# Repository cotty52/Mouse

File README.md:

# Custom Wireless Mouse

This project contains software and hardware designs for a custom wireless mouse. This is an initial prototype intended for me to learn about hardware design and embedded software development. I combined hardware and software files into one repository for easier management. As of 2026-04-21, the design supports basic mouse functionality, including movement, button presses, and scrolling, and is powered by a 3.7V Li-ion battery, rechargeable via USB-C.

## File Structure

```
Mouse/
├── Documents/        # Datasheets, bootloader UF2, 3D models
├── Guide/
│   └── README.md     # New machine setup guide
├── KiCad/            # PCB schematics and layout
└── Software/
    ├── PROJECT_GUIDE.md  # Architecture, task tracking, module reference
    └── ...
```

- `Documents` contains datasheets, reference layouts, and documentation for the nRF Connect SDK and Zephyr project.
- `Guide` contains the new machine setup guide (`Guide/README.md`) and dated snapshots of known-good board/config files.
- `KiCad` contains the KiCad project files for the PCB design (schematics, PCB layout, Gerber files).
- `Software` contains firmware source, board definitions, and configuration files. See `Software/PROJECT_GUIDE.md` for details.

## Hardware Design

The hardware design is based on the nRF52840 because of its popularity/availability, built in Bluetooth, low power consumption, and integration with the nRF SDK for software development. The PCB was designed using KiCad and currently relies on a nRF52840 nice!nano microcontroller for higher level development in the early stages. The microcontroller includes a USB-C port for charging and firmware flashing, a charging protection circuit, and enough GPIO for this project. The design also includes a PMW3389 optical sensor for mouse movement, which is supported by the nRF SDK and Zephyr.

### PCB Images

| Full | Front | Back |
|:---:|:---:|:---:|
|  |  |  |

## Software Design

The software is developed using the nRF Connect SDK, which is based on the Zephyr RTOS. The nRF Connect VS Code extension is used for development, which provides a convenient interface for firmware development. The base structure is copied directly from the nRF Desktop sample project, which provides a good starting point for developing a Bluetooth mouse. The sample provides support for Bluetooth connectivity, mouse movement, button presses, and scrolling out of the box, with additional features available to be toggled on/off using the Kconfig GUI. The sample also provides sample mouse configurations as well as a PMW3360 driver, which is similar to the PMW3389. These files serve as a reference for the development of custom hardware and application files for the custom mouse.

## Current Problems

As of 2026-04-27 there are a couple major issues. The primary issue is the nice!nano board itself. While it was a good microcontroller to get started with this project and to learn about the basics, it was sometimes difficult to work with. Even though there are SWD pads on the back of the board, I could not get it to work with my nRF52840-DK. I also could not get bluetooth to work on the nice!nano, which is why I switched to the nRF52840-dongle for the most recent development. The dongle is meant to be a receiver, but it has enough gpio to connect everything; and since it is a nordic product, development was much easier.

The second problem was with the pmw3389 sensor. I have not figured out why it was not working with my PCB, but I was able to get it working with a breakout board. A multimeter showed that the voltage at the VDD pin was not stable and would start below 1.9V, then rise to above 1.9V. This leads me to believe my step-down circuit is wrong; either I got the calculations for the resistors and capacitors wrong, or the buck converter was not soldered properly. I used a microscope and the connections looked good, but it is very small so it's possible there is a cold solder joint or something else I missed.

## Future Improvements

The next step is to design the PCB without the nice!nano which will require using the nRF52840 SoC directly. This will involve further researching the nRF52840 for proper implementation as well as designing power management and charging circuits. I will also need to decide on whether to use an SoC with an included antenna or design one myself.

Becasue of the problems with the pmw3389, I will not use the TPS62821DLCR buck converter. I will probably use a linear step-down regulator instead, which will be less efficient but much simpler to implement.

On the software side, the next step is to develop custom application code for the mouse which will allow users to customize the behavior of the mouse, such as button mapping and sensitivity settings.

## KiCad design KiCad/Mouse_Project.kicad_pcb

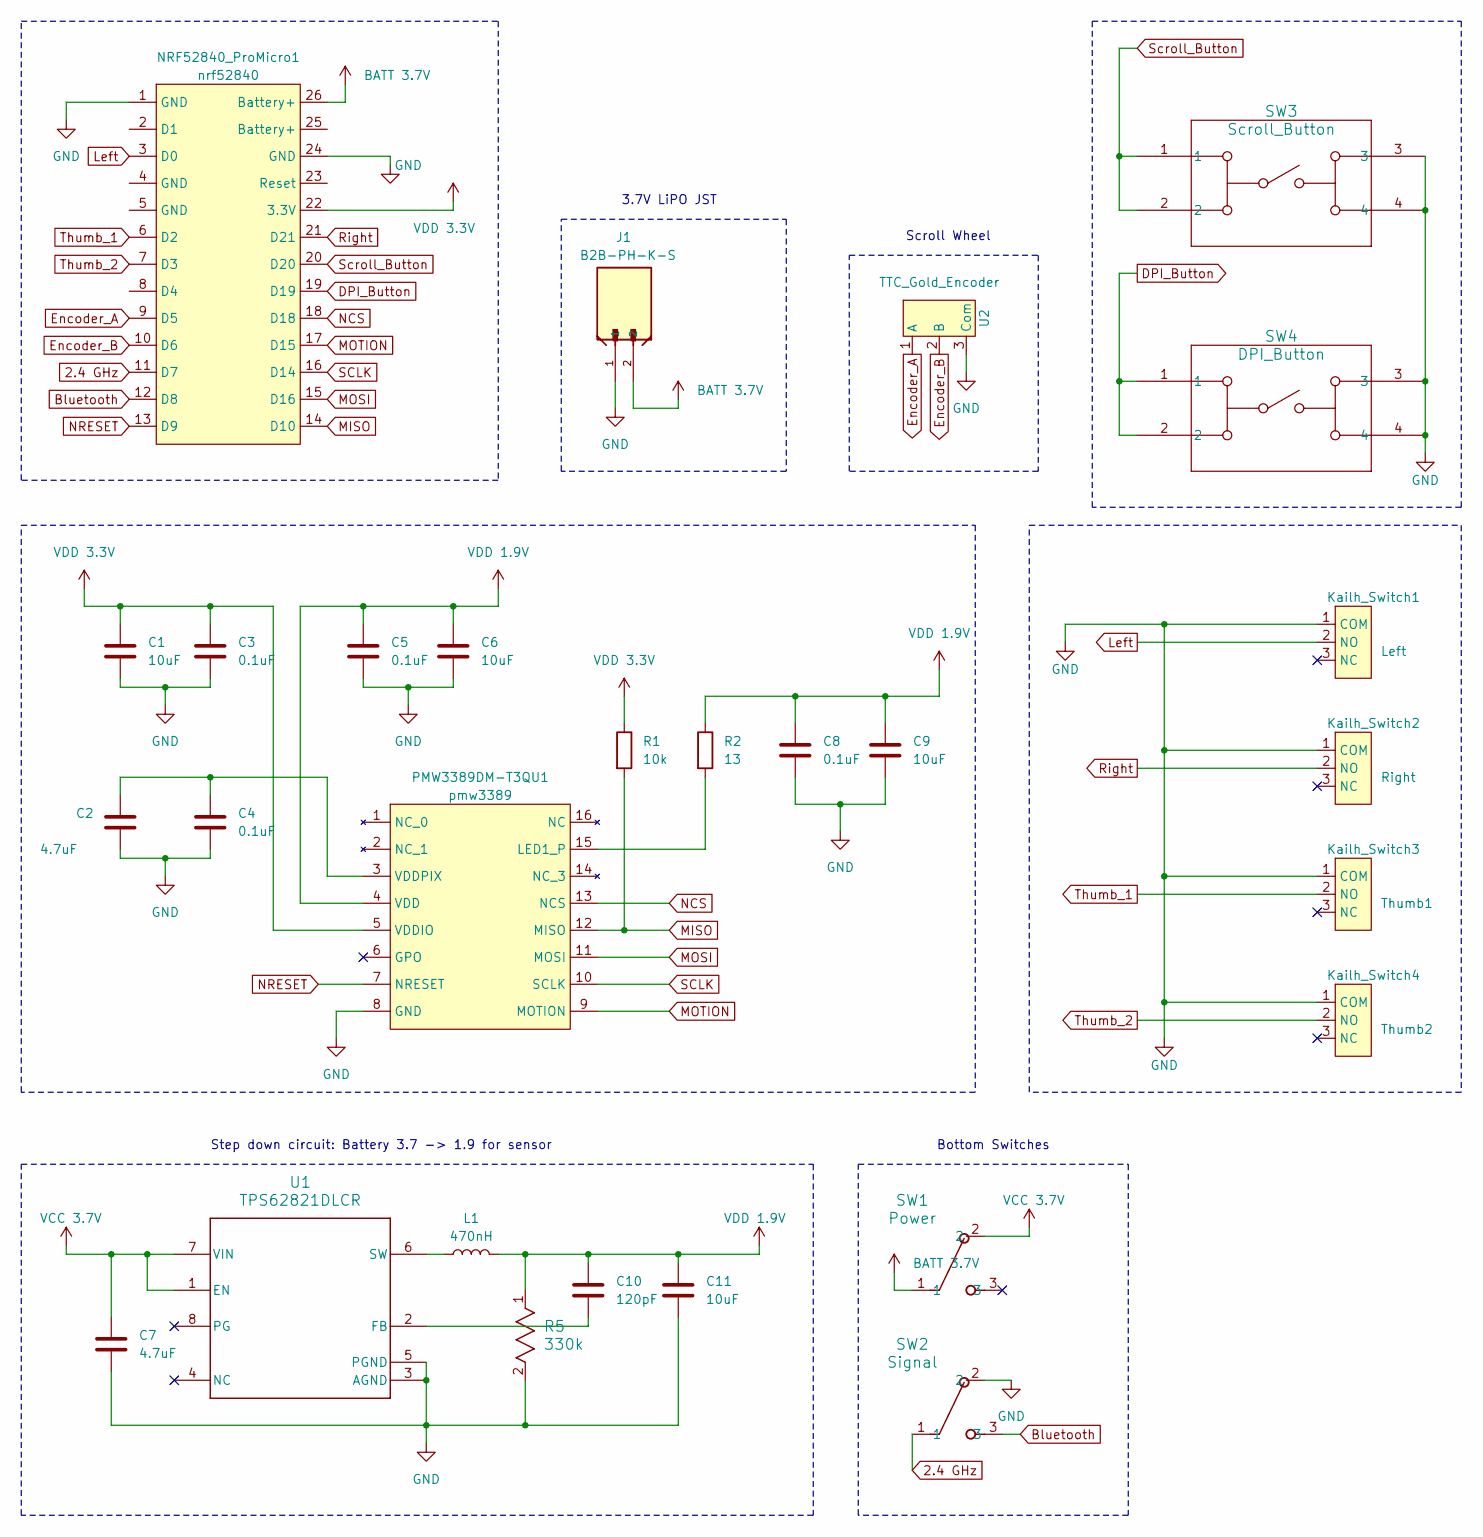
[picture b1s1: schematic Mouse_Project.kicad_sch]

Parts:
C1, C6, C9, C11: 10uF; CL31A106KBHNNNE
C2, C7: 4.7uF; CL31B475KBHNNNE
C3, C4, C5, C8: 0.1uF; C1206C104K5RACTU
C10: 120pF; C0805C121J5GACTU
J1: B2B-PH-K-S; CONN2_B2B-PH-K-S_JST
Kailh_Switch1: Left; Kailh_Switch
Kailh_Switch2: Right; Kailh_Switch
Kailh_Switch3: Thumb1; Kailh_Switch
Kailh_Switch4: Thumb2; Kailh_Switch
L1: 470nH; DFE252012P-1R0M=P2
NRF52840_ProMicro1: nrf52840; nrf52840_promicro
PMW3389DM-T3QU1: pmw3389; pmw3389dm-t3qu
R1: 10k; RC1206FR-0710KL
R2: 13; RC0805N_YAG
R5: 330k; RES_CRGCQ1206F330K_TEC
SW1: Power; SW_1218_EWI
SW2: Signal; SW_1218_EWI
SW3: Scroll_Button; SW4_1825910-B_TEC
SW4: DPI_Button; SW4_1825910-B_TEC
U1: TPS62821DLCR
U2: TTC_Gold_Encoder

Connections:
2.4 GHz: NRF52840_ProMicro1.11 (D7), SW2.1
BATT 3.7V: J1.2, NRF52840_ProMicro1.26 (Battery+), SW1.1
Bluetooth: NRF52840_ProMicro1.12 (D8), SW2.3
DPI_Button: NRF52840_ProMicro1.19 (D19), SW4.1, SW4.2
Encoder_A: NRF52840_ProMicro1.9 (D5), U2.1 (A)
Encoder_B: NRF52840_ProMicro1.10 (D6), U2.2 (B)
GND: C1.2, C2.2, C3.2, C4.2, C5.2, C6.2, C7.2, C8.2, C9.2, C11.2, J1.1, Kailh_Switch1.1 (COM), Kailh_Switch2.1 (COM), Kailh_Switch3.1 (COM), Kailh_Switch4.1 (COM), NRF52840_ProMicro1.1 (GND), NRF52840_ProMicro1.24 (GND), PMW3389DM-T3QU1.8 (GND), R5.2, SW2.2, SW3.3, SW3.4, SW4.3, SW4.4, U1.3 (AGND), U1.5 (PGND), U2.3 (Com)
Left: Kailh_Switch1.2 (NO), NRF52840_ProMicro1.3 (D0)
MISO: NRF52840_ProMicro1.14 (D10), PMW3389DM-T3QU1.12 (MISO), R1.2
MOSI: NRF52840_ProMicro1.15 (D16), PMW3389DM-T3QU1.11 (MOSI)
MOTION: NRF52840_ProMicro1.17 (D15), PMW3389DM-T3QU1.9 (MOTION)
NCS: NRF52840_ProMicro1.18 (D18), PMW3389DM-T3QU1.13 (NCS)
NRESET: NRF52840_ProMicro1.13 (D9), PMW3389DM-T3QU1.7 (NRESET)
unnamed: PMW3389DM-T3QU1.15 (LED1_P), R2.2
unnamed: C2.1, C4.1, PMW3389DM-T3QU1.3 (VDDPIX)
unnamed: C10.2, U1.2 (FB)
unnamed: L1.1, U1.6 (SW)
Right: Kailh_Switch2.2 (NO), NRF52840_ProMicro1.21 (D21)
SCLK: NRF52840_ProMicro1.16 (D14), PMW3389DM-T3QU1.10 (SCLK)
Scroll_Button: NRF52840_ProMicro1.20 (D20), SW3.1, SW3.2
Thumb_1: Kailh_Switch3.2 (NO), NRF52840_ProMicro1.6 (D2)
Thumb_2: Kailh_Switch4.2 (NO), NRF52840_ProMicro1.7 (D3)
VCC 3.7V: C7.1, SW1.2, U1.1 (EN), U1.7 (VIN)
VDD 1.9V: C5.1, C6.1, C8.1, C9.1, C10.1, C11.1, L1.2, PMW3389DM-T3QU1.4 (VDD), R2.1, R5.1
VDD 3.3V: C1.1, C3.1, NRF52840_ProMicro1.22 (3.3V), PMW3389DM-T3QU1.5 (VDDIO), R1.1

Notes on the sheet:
Step down circuit: Battery 3.7 -> 1.9 for sensor
Scroll Wheel
Bottom Switches
3.7V LiPO JST

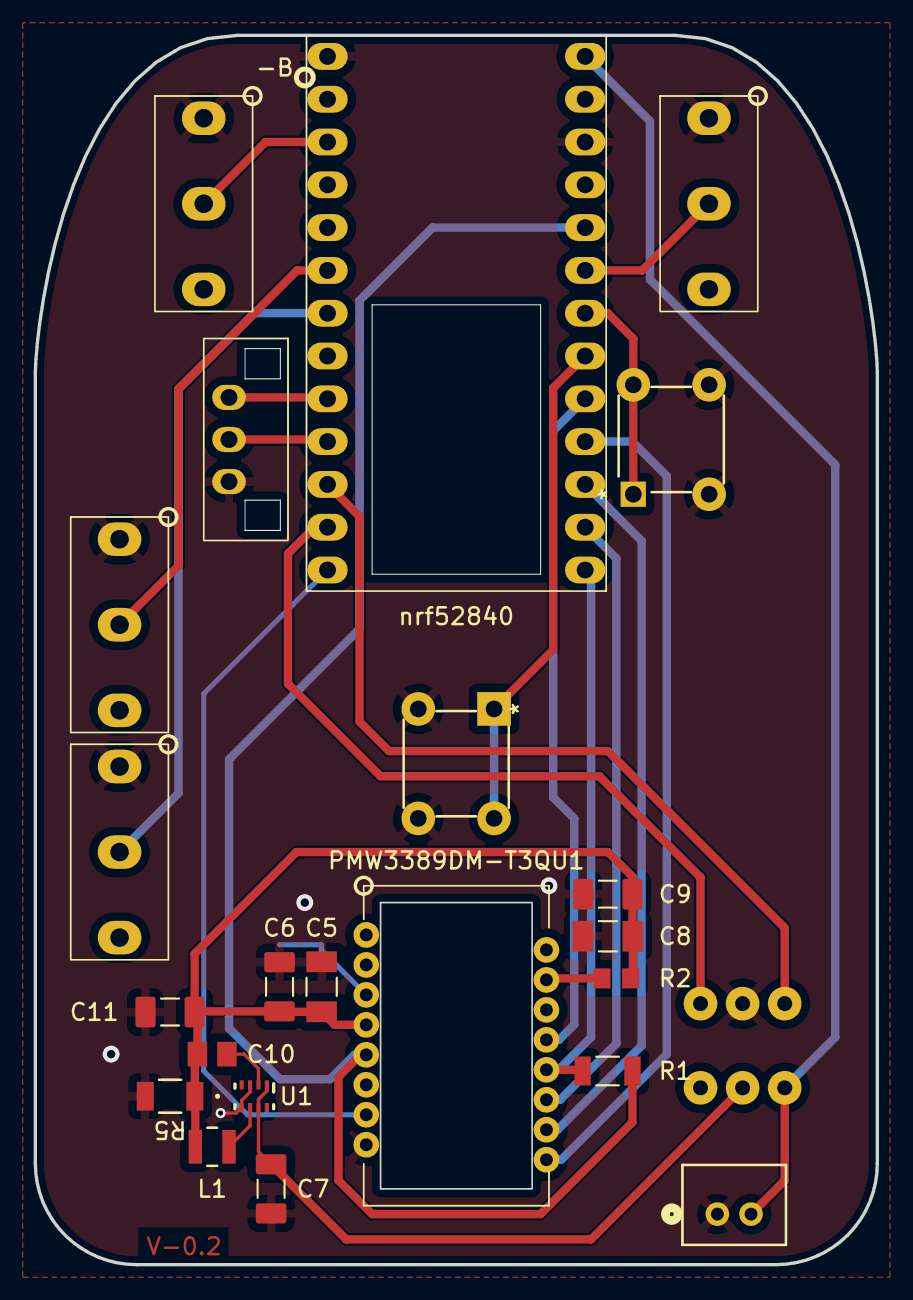
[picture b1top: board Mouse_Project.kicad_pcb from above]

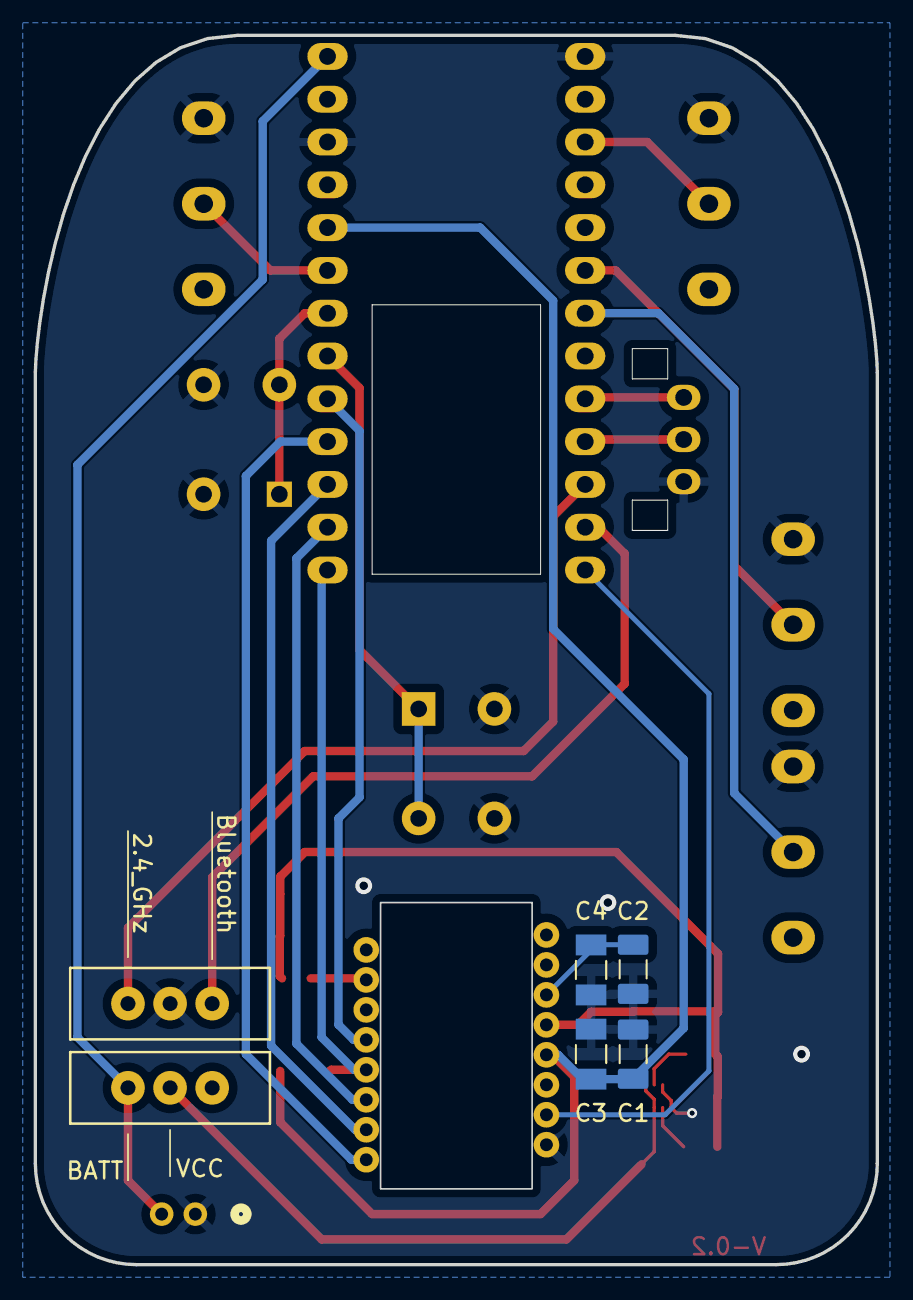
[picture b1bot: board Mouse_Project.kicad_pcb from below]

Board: 2 copper layers, 50.0 x 73.0 mm, 28 parts (6 on the bottom side), 25 nets.

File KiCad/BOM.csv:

"Reference","Value","Qty","Datasheet","Footprint","DNP"
"C1,C6,C9,C11","10uF","4","~","CL21A106KOQNNNE:CAP_CL21_SAM",""
"C2","4.7uF/10V","1","~","CL10A475KP8NNNC:CAP_0603_CL10A_1P6XP8_SAM",""
"C3,C4,C5,C8","0.1uF","4","~","CL10B104KB8NNNC:CAP_CL10_SAM",""
"C7","4.7uF","1","~","CL10A475KP8NNNC:CAP_0603_CL10A_1P6XP8_SAM",""
"C10","120pF","1","~","GRM0335C1H121JA01D:G-033_MUR",""
"J1","B2B-PH-K-S","1","","B2B-PH-K-S:CONN2_B2B-PH-K-S_JST",""
"Kailh_Switch1","Left","1","","Kailh_Switch:Kailh_Switch",""
"Kailh_Switch2","Right","1","","Kailh_Switch:Kailh_Switch",""
"Kailh_Switch3","Thumb1","1","","Kailh_Switch:Kailh_Switch",""
"Kailh_Switch4","Thumb2","1","","Kailh_Switch:Kailh_Switch",""
"L1","470nH","1","~","CIGT201610EHR47MNE:RES_CIGT201610",""
"NRF52840_ProMicro1","nrf52840","1","","nrf52840_promicro:nrf52840_promicro",""
"PMW3389DM-T3QU1","pmw3389","1","","pmw3389dm-t3qu:pmw3389dm-t3qu",""
"R1","10k","1","~","RC1005F103CS:RES_1005_SAM",""
"R2","13","1","~","RC0805FR_0713RL:RC0805N_YAG",""
"R5","CRGCQ1206F330K","1","CRGCQ1206F330K","RES_CRGCQ1206F330K_TEC",""
"SW1","Power","1","EG1218","SW_1218_EWI",""
"SW2","Signal","1","EG1218","SW_1218_EWI",""
"SW3","Scroll_Button","1","1825910-6","1825910-6:SW4_1825910-B_TEC",""
"SW4","DPI_Button","1","1825910-6","1825910-6:SW4_1825910-B_TEC",""
"U1","TPS62821DLCR","1","TPS62821DLCR","TPS62821DLCR:TPS62821DLCR",""
"U2","TTC_Gold_Encoder","1","","TTC_Gold_Encoder:TTC_Gold_Encoder",""

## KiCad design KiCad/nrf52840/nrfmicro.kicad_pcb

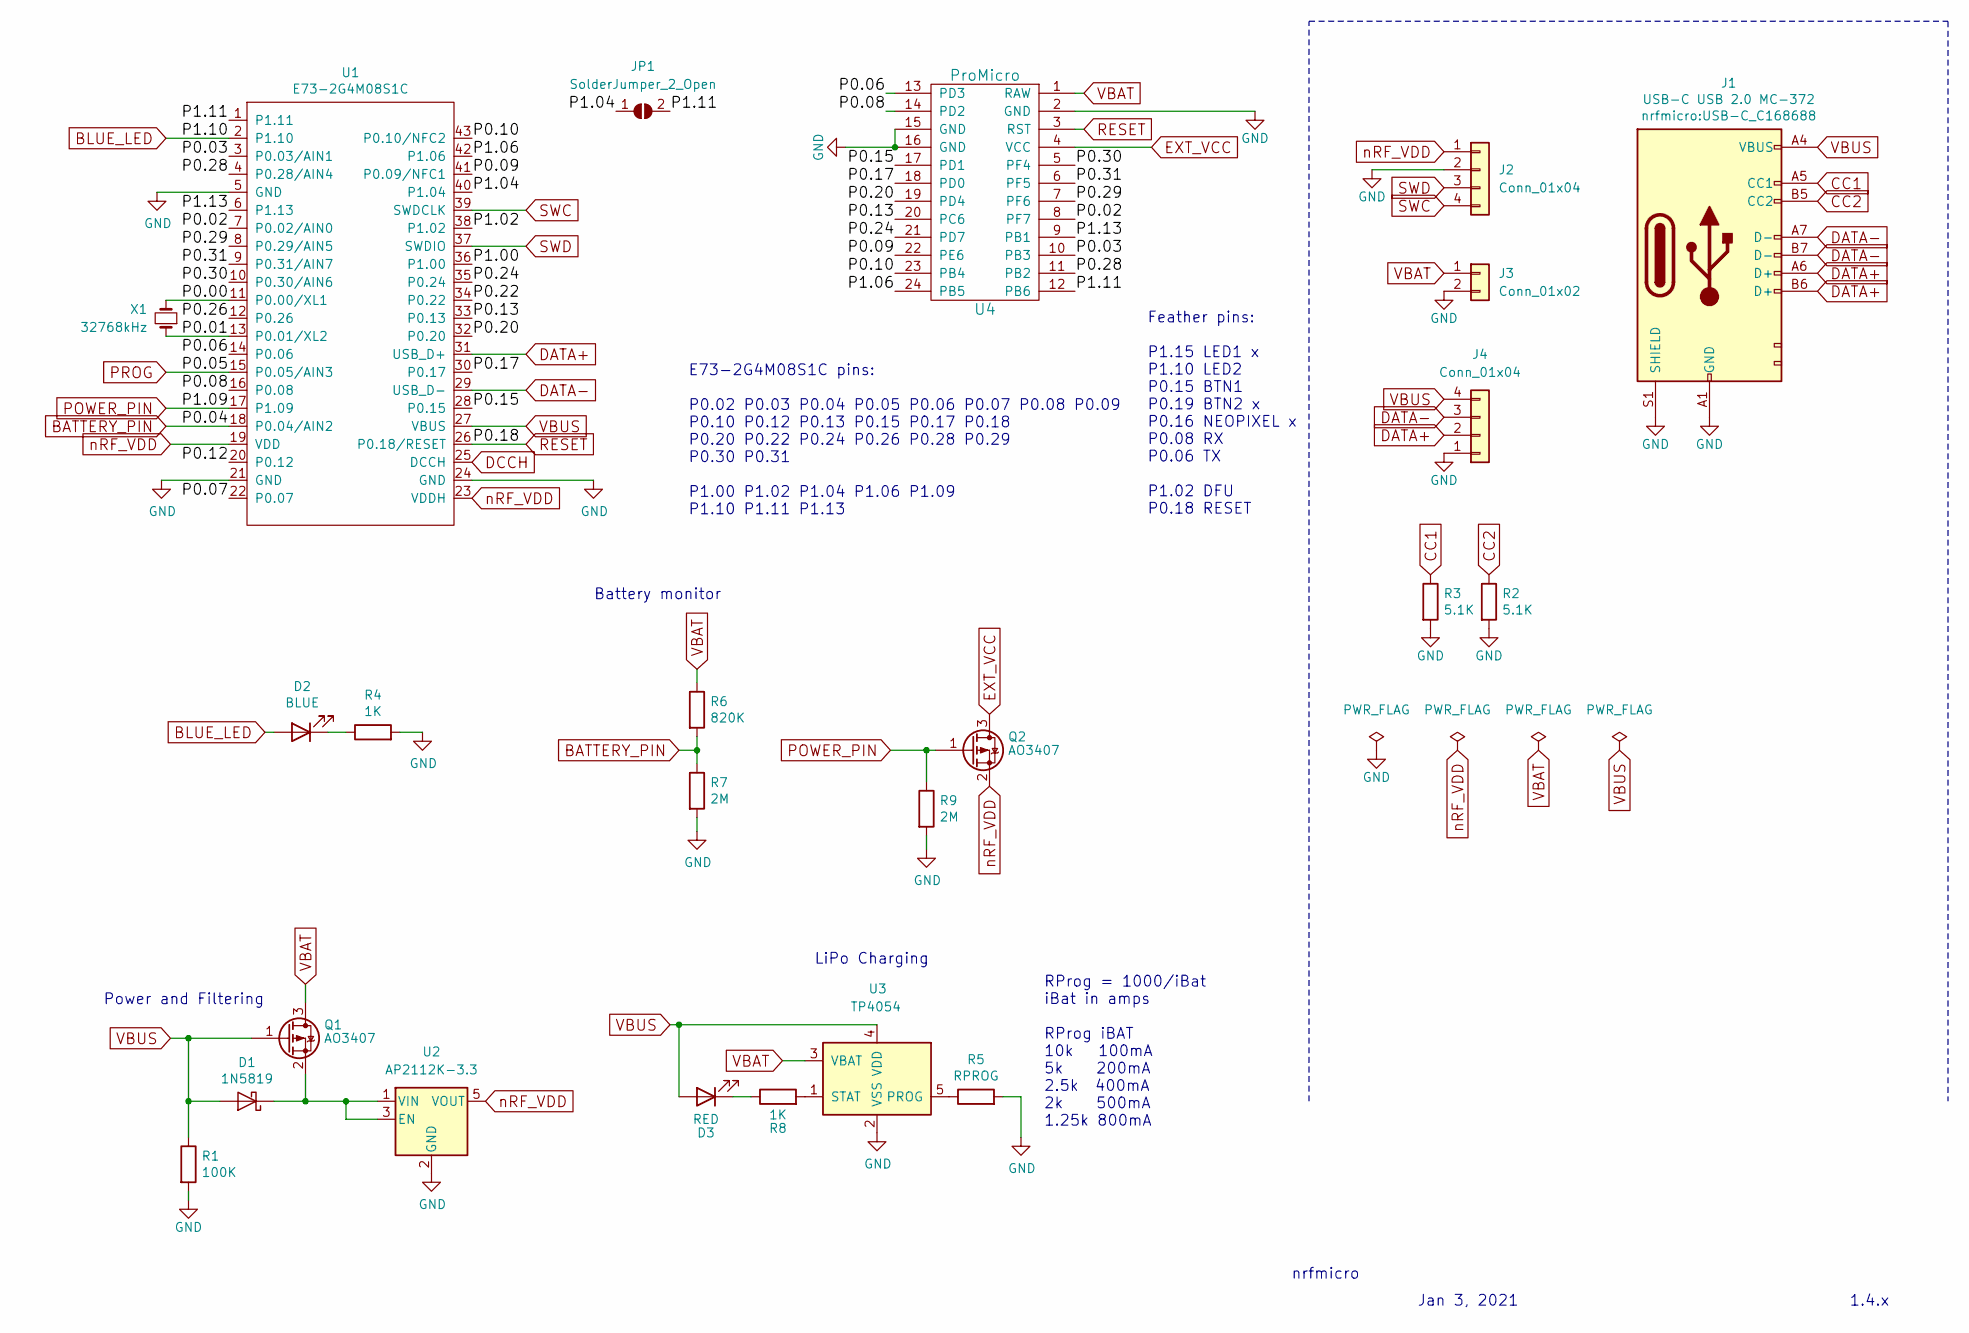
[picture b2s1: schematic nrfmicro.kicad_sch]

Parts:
D1: 1N5819; D_SOD-323F
D2: BLUE; LED_0603_1608Metric
D3: RED; LED_0603_1608Metric
J1: USB-C USB 2.0 MC-372; USB-C_C168688
J2: Conn_01x04; connector_swd
J3: Conn_01x02
J4: Conn_01x04; connector_usb
JP1: SolderJumper_2_Open; Jumper_SMD
Q1, Q2: AO3407; SOT-23
R1: 100K; R_0603_1608Metric
R2, R3: 5.1K; R_0603_1608Metric
R4, R8: 1K; R_0603_1608Metric
R5: RPROG; R_0603_1608Metric
R6: 820K; R_0603_1608Metric
R7, R9: 2M; R_0603_1608Metric
U1: E73-2G4M08S1C; E73-2G4M08S1C-52840
U2: AP2112K-3.3; SOT-23-5
U3: TP4054; SOT-23-5
U4: ProMicro; pro_micro
X1: 32768kHz

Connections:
/P0.00: U1.11 (P0.00/XL1), X1.2
/P0.01: U1.13 (P0.01/XL2), X1.1
/P0.02: U1.7 (P0.02/AIN0), U4.8 (PF7)
/P0.03: U1.3 (P0.03/AIN1), U4.10 (PB3)
/P0.06: U1.14 (P0.06), U4.13 (PD3)
/P0.07: U1.22 (P0.07)
/P0.08: U1.16 (P0.08), U4.14 (PD2)
/P0.09: U1.41 (P0.09/NFC1), U4.22 (PE6)
/P0.10: U1.43 (P0.10/NFC2), U4.23 (PB4)
/P0.12: U1.20 (P0.12)
/P0.13: U1.33 (P0.13), U4.20 (PC6)
/P0.15: U1.28 (P0.15), U4.17 (PD1)
/P0.17: U1.30 (P0.17), U4.18 (PD0)
/P0.20: U1.32 (P0.20), U4.19 (PD4)
/P0.22: U1.34 (P0.22)
/P0.24: U1.35 (P0.24), U4.21 (PD7)
/P0.26: U1.12 (P0.26)
/P0.28: U1.4 (P0.28/AIN4), U4.11 (PB2)
/P0.29: U1.8 (P0.29/AIN5), U4.7 (PF6)
/P0.30: U1.10 (P0.30/AIN6), U4.5 (PF4)
/P0.31: U1.9 (P0.31/AIN7), U4.6 (PF5)
/P1.00: U1.36 (P1.00)
/P1.02: U1.38 (P1.02)
/P1.04: JP1.1 (A), U1.40 (P1.04)
/P1.06: U1.42 (P1.06), U4.24 (PB5)
/P1.11: JP1.2 (B), U1.1 (P1.11), U4.12 (PB6)
/P1.13: U1.6 (P1.13), U4.9 (PB1)
BATTERY_PIN: R6.2, R7.1, U1.18 (P0.04/AIN2)
BLUE_LED: D2.2 (A), U1.2 (P1.10)
CC1: J1.A5 (CC1), R3.1
CC2: J1.B5 (CC2), R2.1
DATA+: J1.A6 (D+), J1.B6 (D+), J4.2, U1.31 (USB_D+)
DATA-: J1.A7 (D-), J1.B7 (D-), J4.3, U1.29 (USB_D-)
DCCH: U1.25 (DCCH)
EXT_VCC: Q2.3 (D), U4.4 (VCC)
GND: J1.A1 (GND), J1.S1 (SHIELD), J2.2, J3.2, J4.1, R1.2, R2.2, R3.2, R4.2, R5.2, R7.2, R9.2, U1.5 (GND), U1.21 (GND), U1.24 (GND), U2.2 (GND), U3.2 (VSS), U4.2 (GND), U4.15 (GND), U4.16 (GND)
unnamed: D1.1 (K), Q1.2 (S), U2.1 (VIN), U2.3 (EN)
unnamed: D2.1 (K), R4.1
unnamed: D3.1 (K), R8.1
unnamed: R5.1, U3.5 (PROG)
unnamed: R8.2, U3.1 (STAT)
POWER_PIN: Q2.1 (G), R9.1, U1.17 (P1.09)
PROG: U1.15 (P0.05/AIN3)
RESET: U1.26 (P0.18/RESET), U4.3 (RST)
SWC: J2.4, U1.39 (SWDCLK)
SWD: J2.3, U1.37 (SWDIO)
VBAT: J3.1, Q1.3 (D), R6.1, U3.3 (VBAT), U4.1 (RAW)
VBUS: D1.2 (A), D3.2 (A), J1.A4 (VBUS), J4.4, Q1.1 (G), R1.1, U1.27 (VBUS), U3.4 (VDD)
nRF_VDD: J2.1, Q2.2 (S), U1.19 (VDD), U1.23 (VDDH), U2.5 (VOUT)

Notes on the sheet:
LiPo Charging
Jan 3, 2021
1.4.x
RProg = 1000/iBat iBat in amps RProg iBAT 10k 100mA 5k 200mA 2.5k 400mA 2k 500mA 1.25k 800mA
Power and Filtering
nrfmicro
Battery monitor
E73-2G4M08S1C pins: P0.02 P0.03 P0.04 P0.05 P0.06 P0.07 P0.08 P0.09 P0.10 P0.12 P0.13 P0.15 P0.17 P0.18 P0.20 P0.22 P0.24 P0.26 P0.28 P0.29 P0.30 P0.31 P1.00 P1.02 P1.04 P1.06 P1.09 P1.10 P1.11 P1.13
Feather pins: P1.15 LED1 x P1.10 LED2 P0.15 BTN1 P0.19 BTN2 x P0.16 NEOPIXEL x P0.08 RX P0.06 TX P1.02 DFU P0.18 RESET

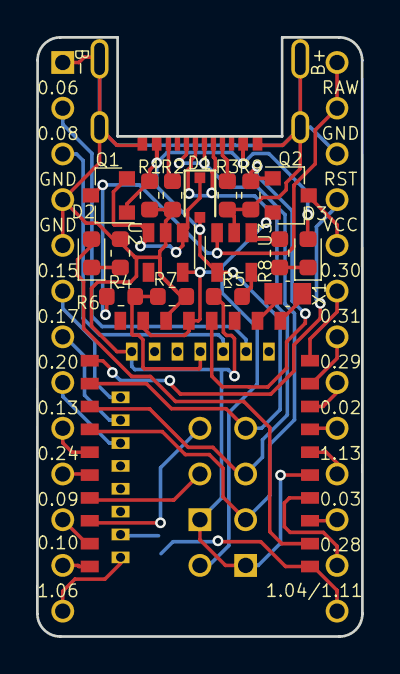
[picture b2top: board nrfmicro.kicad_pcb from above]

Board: 2 copper layers, 18.1 x 33.3 mm, 24 parts (1 on the bottom side), 41 nets.

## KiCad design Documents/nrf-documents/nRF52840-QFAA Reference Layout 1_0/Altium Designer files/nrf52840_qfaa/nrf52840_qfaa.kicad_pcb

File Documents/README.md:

# Documents sub-directory structure

## File Structure
```
Documents
├── README.md
├── nrf-documents
│   ├── nrf52840-data-sheet.pdf
│   ├── nRF52840-QFAA Reference Layout 1_0
│   ├── nrf52840-qfaa-reference-layout-1_0.zip
│   ├── nrf_connect_sdk_-_latest_board_porting_guide_2026-02-05-12-19-40.pdf
│   └── nrf_connect_sdk_-_latest_zephyr_project_documentation_2026-02-05-12-22-21.pdf
├── zmk-driver-pmw3389-main
├── pmw3389_zephyr_driver
├── nrf-Dongle.3mf
└── update-nice_nano_bootloader-0.9.2_nosd.uf2
```

### Bootloader
- `update-nice_nano_bootloader-0.9.2_nosd.uf2`: The UF2 file for updating the Nice!Nano bootloader to version 0.9.2

This bootloader can be downloaded from the adafruit/Adafruit_nRF52_Bootloader github repository: https://github.com/adafruit/Adafruit_nRF52_Bootloader/releases

To use the bootloader:
  1. Plug the nice!nano into your computer.  
  2. Touch ground and reset together twice within ~0.5 seconds to enter bootloader mode.  
  3. The nice!nano should appear as a USB drive.  
  4. Drag and drop the `update-nice_nano_bootloader-0.9.2_nosd.uf2` file onto the nice!nano USB drive to update the bootloader.  

This process is the same as any other .uf2 file you would use to flash firmware.

### nRF Documents
- `nrf-documents`: A collection of documents related to the nRF52840 SoC, including datasheets, reference layouts, and documentation for the nRF Connect SDK and Zephyr project.

Here is a list of links to helpful resources on the Nordic Semiconductor website:
- [nRF Sample Projects] https://docs.nordicsemi.com/bundle/ncs-3.1.1/page/nrf/samples.html
- [nRF52840 DK] https://docs.nordicsemi.com/bundle/ug_nrf52840_dk/page/UG/dk/ext_programming_support_P20.html
- [nRF52840 Reference Layout] https://docs.nordicsemi.com/bundle/ncs-latest/page/zephyr/hardware/porting/board_porting.html
- [nRF52840 PMW3360 Driver] https://docs.nordicsemi.com/bundle/ncs-3.1.1/page/nrf/drivers/pmw3360.html
- [nRF52840 Features] https://docs.nordicsemi.com/bundle/ncs-3.1.1/page/nrf/app_dev/device_guides/nrf52/features.html
- [nRF52840 Bootloader Quick Start] https://docs.nordicsemi.com/bundle/ncs-3.1.1/page/nrf/app_dev/bootloaders_dfu/mcuboot_nsib/bootloader_quick_start.html
- [nRF52840 Desktop Application] https://docs.nordicsemi.com/bundle/ncs-latest/page/nrf/applications/nrf_desktop/README.html
- [nRF Connect VS Code] https://docs.nordicsemi.com/bundle/nrf-connect-vscode/page/guides/bd_boards_devices.html
- [nRF52840 Board Porting] https://docs.nordicsemi.com/bundle/ncs-latest/page/zephyr/hardware/porting/board_porting.html#transition_to_the_current_hardware_model
- [nRF52840 Installation] https://docs.nordicsemi.com/bundle/ncs-3.2.2/page/nrf/installation/install_ncs.html
- [nRF52840 Dongle Documentation] https://docs.nordicsemi.com/bundle/ncs-latest/page/zephyr/boards/nordic/nrf52840dongle/doc/index.html
- [Nordic Academy] https://academy.nordicsemi.com/

### PMW3389 Driver
- `zmk-driver-pmw3389-main`: This is a cloned repository of the PMW3389 driver for ZMK, which can be found at https://github.com/grassfedreeve/zmk-driver-pmw3389. I based my driver off of this repository.
- `pmw3389_zephyr_driver`: Another repository I found after I already finished my driver. As of 2026-04-21 I have not looked through the code, but it has been worked on within the past week so it may provide additional features or optimizations. Here is the link: https://github.com/teamspatzenhirn/pmw3389_zephyr_driver/tree/main. Acording to their bio, this actually was created by Team Spatzenhirn - Uni Ulm, Carolo-Cup team from Ulm University.

The nRF Desktop sample provides a driver for the pmw3360, which is similar. The link to the driver is above; the files can also be found in the ~/ncs directory when installing the nRF Connect SDK.

### nRF Dongle 3MF
- `nrf-Dongle.3mf`: A 3D printable case for the nRF52840 Dongle. Created by AIR VIT-AP and put on MakerWorld: https://makerworld.com/en/models/1107675-opensk-case-for-nrf52480dongle?from=search#profileId-1483028

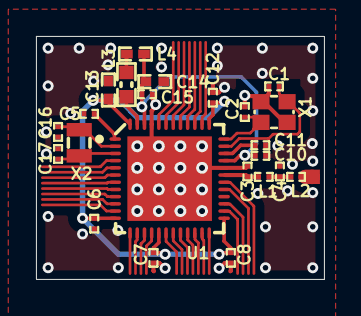
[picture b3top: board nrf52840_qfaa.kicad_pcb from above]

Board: 2 copper layers, 16.0 x 13.5 mm, 23 parts (0 on the bottom side), 13 nets.

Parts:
C1, C2, C16, C17: 12pF; CAPC0603X03L_C
C3: 1.0pF; CAPC0603X03L_C
C4: 1.2pF; CAPC0603X03L_C
C5, C6, C7, C8, C12: 100nF; CAPC0603X03L_C
C10: N.C.; CAPC0603X03L_C_NC
C11: 100pF; CAPC0603X03L_C
C13, C14: 1.0µF; CAPC1005X04L
C15: 47nF; CAPC0603X03L_C
L1: 4.7nH; INDC0603X03L_C
L2: 2.2nH; INDC0603X03L_C
L3: 10µH; INDC1608X06L
L4: 15nH; INDC1005X04L
U1: nRF52840-QFAA; QFN40P600X600X90-48N
X1: 32MHz; XTAL_2016_NT
X2: 32.768kHz; XTAL_2012

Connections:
DEC1: C5.1, U1.1
DEC3: C11.1, U1.34
DEC4_6: C10.2, C14.2, C15.1, L4.1, U1.33, U1.46
GND: C1.2, C2.2, C3.1, C4.1, C5.2, C6.2, C7.2, C8.2, C10.1, C11.2, C12.2, C13.2, C14.1, C15.2, C16.2, C17.2, U1.32, U1.45, U1.49, X1.2
NetC3_2: C3.2, L1.1, U1.31
NetC4_2: C4.2, L1.2, L2.1
NetL3_1: L3.1, L4.2
NetL3_2: L3.2, U1.47
P0.00/XL1: C16.1, U1.2, X2.1
P0.01/XL2: C17.1, U1.3, X2.2
VDD_NRF: C6.1, C7.1, C8.1, C12.1, C13.1, U1.12, U1.17, U1.25, U1.37, U1.48
XC1: C1.1, U1.35, X1.1
XC2: C2.1, U1.36, X1.3

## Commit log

2024-12-05 gitignore
2025-02-19 updated stuff
2025-02-25 backup
2025-03-01 Almost done
2025-03-01 stuff
2025-03-05 Completed version 0.1
2025-03-17 code for v1
2025-03-19 testing platform.io
2025-11-13 Lots of edits. Partial reorganizing.
2025-11-14 A little organization
2025-11-15 potentially working
2025-11-20 PCB v0.2 almost done
2025-11-21 Enhance agent documentation with project details
    Expanded the agent's documentation to include core identity, project knowledge, and workflow for diagnosing issues in the nRF Desktop Mouse project.
2025-11-21 removed files
2026-01-30 upload 2026/1/30
2026-01-30 Completed v0.2
    Ordered new PCB and components
2026-04-07 upload 2026-04-07
2026-04-21 Upload 2026-04-21. Added untracked work and some documentation files.
2026-04-27 Everything works with the nordic dongle. Bluetooth, mouse buttons, sensor.
2026-04-29 Upload 2026-04-29
2026-04-30 Upload 2026-04-30 added PCB images to README
